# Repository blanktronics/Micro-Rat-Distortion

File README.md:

# Overview
Micro Rat Distortion majorly influnced by Olinthus Designs mini effects.

The idea is simple, I wanted to challenge myself by trying to recreate an extremely small version of the ProCo Rat distortion.

My secondary challenge is I want to create something even smaller than the Olinthus Desgin effects.

So far the dimesions of my project mostly mimcs the Olinthus dimensions except my assembly is 50mils wider and 50 mils thinner.

Next steps are to just shrink shrink shrink.

If you would like to try this out for yourself, the KiCad project I've designed can found in this repository!

## Pictures
Here are some pictures of the progress so far.

|  |  |  |  |
| ------- | ------- | ------- | ------- |
|  |  |  |  |
|  | |

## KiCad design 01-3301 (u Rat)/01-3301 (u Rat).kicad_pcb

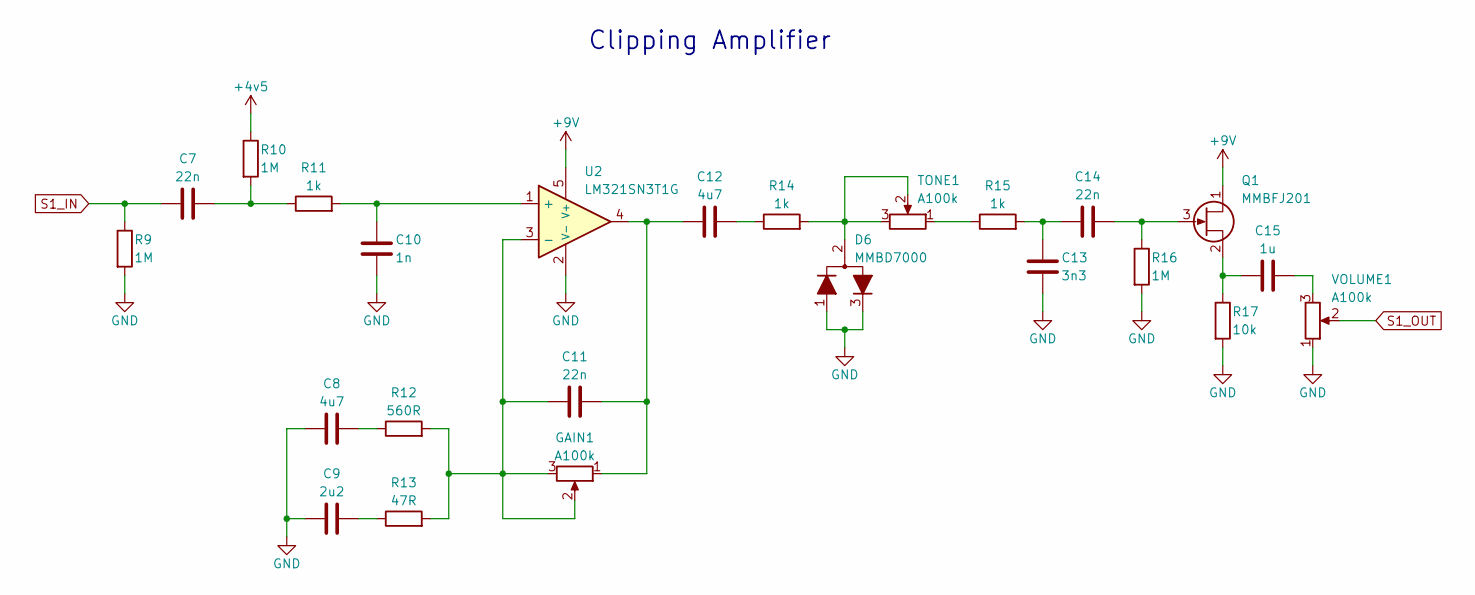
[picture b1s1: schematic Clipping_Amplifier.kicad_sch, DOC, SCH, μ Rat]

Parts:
C7, C11, C14: 22n; C_0402_1005Metric
C8, C12: 4u7; C_0603_1608Metric
C9: 2u2; C_0603_1608Metric
C10: 1n; C_0402_1005Metric
C13: 3n3; C_0402_1005Metric
C15: 1u; C_0603_1608Metric
D6: MMBD7000; SOT-23-3
GAIN1: A100k; Potentiometer_Alpha_RD901F-40-00D_Single_Vertical
Q1: MMBFJ201; SOT-23; Manufacturer_Part_Number MMBFJ201; Mouser Part Number 512-MMBFJ201
R9, R10, R16: 1M; R_0402_1005Metric
R11, R14, R15: 1k; R_0402_1005Metric
R12: 560R; R_0402_1005Metric
R13: 47R; R_0402_1005Metric
R17: 10k; R_0402_1005Metric
TONE1: A100k; Potentiometer_Alpha_RD901F-40-00D_Single_Vertical
U2: LM321SN3T1G; SOT95P275X110-5N; Manufacturer_Part_Number LM321SN3T1G; Mouser Part Number 863-LM321SN3T1G
VOLUME1: A100k; Potentiometer_Alpha_RD901F-40-00D_Single_Vertical

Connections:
+4v5: R10.1; also elsewhere on the board
+9V: Q1.1 (D), U2.5 (V+); also elsewhere on the board
GND: C8.1, C9.1, C10.2, C13.2, D6.1 (A), D6.3 (K), R9.2, R16.2, R17.2, U2.2 (V-), VOLUME1.1; also elsewhere on the board
unnamed: C7.2, R10.2, R11.1
unnamed: C8.2, R12.1
unnamed: C9.2, R13.1
unnamed: C11.2, C12.1, GAIN1.1, U2.4
unnamed: C12.2, R14.1
unnamed: C13.1, C14.1, R15.2
unnamed: C15.2, VOLUME1.3
unnamed: D6.2 (common), R14.2, TONE1.2, TONE1.3
unnamed: C14.2, Q1.3 (G), R16.1
unnamed: C15.1, Q1.2 (S), R17.1
unnamed: R15.1, TONE1.1
unnamed: C10.1, R11.2, U2.1 (+)
unnamed: C11.1, GAIN1.2, GAIN1.3, R12.2, R13.2, U2.3 (-)
S1_IN: C7.1, R9.1; also elsewhere on the board
S1_OUT: VOLUME1.2; also elsewhere on the board

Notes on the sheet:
Clipping Amplifier

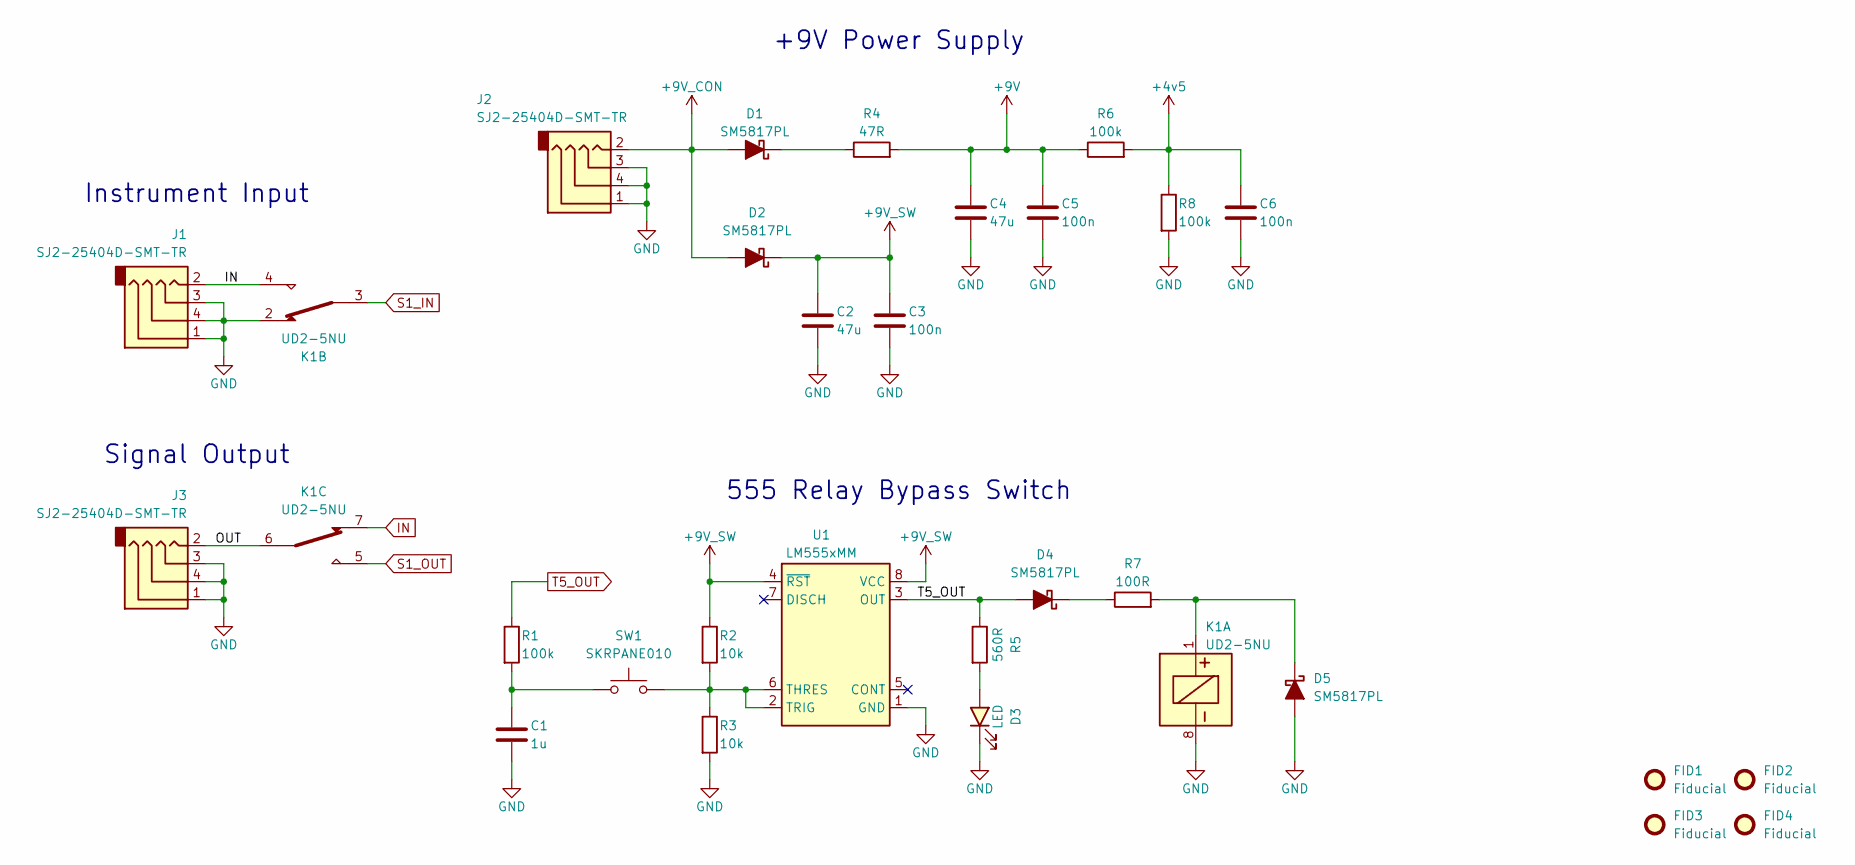
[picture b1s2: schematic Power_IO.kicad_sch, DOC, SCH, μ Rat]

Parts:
C1: 1u; C_0603_1608Metric
C2, C4: 47u; C_1210_3225Metric
C3, C5, C6: 100n; C_0402_1005Metric
D1, D2, D4, D5: SM5817PL; D_SOD-123
D3: LED; LED_0603_1608Metric
FID1, FID2, FID3, FID4: Fiducial; Fiducial_0.5mm_Mask1mm
J1, J2, J3: SJ2-25404D-SMT-TR; SJ225404DSMTTR; Manufacturer_Part_Number SJ2-25404D-SMT-TR; Mouser Part Number 490-SJ2-25404DSMT-TR
K1: UD2-5NU; UD25NUN; Manufacturer_Part_Number UD2-5NU; Mouser Part Number 551-UD2-5NU
R1, R6, R8: 100k; R_0402_1005Metric
R2, R3: 10k; R_0402_1005Metric
R4: 47R; R_0402_1005Metric
R5: 560R; R_0402_1005Metric
R7: 100R; R_0402_1005Metric
SW1: SKRPANE010
U1: LM555xMM; VSSOP-8_3x3mm_P0.65mm

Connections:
+4v5: C6.1, R6.2, R8.1; also elsewhere on the board
+9V: C4.1, C5.1, R4.2, R6.1; also elsewhere on the board
+9V_CON: D1.2 (A), D2.2 (A), J2.2 (TIP)
+9V_SW: C2.1, C3.1, D2.1 (K), R2.1, U1.4 (~RST), U1.8 (VCC)
/Power IO/OUT: J3.2 (TIP), K1.6 (COM_2)
GND: C1.2, C2.2, C3.2, C4.2, C5.2, C6.2, D3.1 (K), D5.2 (A), J1.1 (SLEEVE), J1.3 (RING1), J1.4 (RING2), J2.1 (SLEEVE), J2.3 (RING1), J2.4 (RING2), J3.1 (SLEEVE), J3.3 (RING1), J3.4 (RING2), K1.2 (NC_1), K1.8 (COIL_-), R3.2, R8.2, U1.1 (GND); also elsewhere on the board
IN: J1.2 (TIP), K1.4 (NO_1), K1.7 (NC_2)
unnamed: C1.1, R1.2, SW1.1
unnamed: D1.1 (K), R4.1
unnamed: D3.2 (A), R5.2
unnamed: D4.1 (K), R7.1
unnamed: D5.1 (K), K1.1 (COIL_+), R7.2
unnamed: R2.2, R3.1, SW1.2, U1.2 (TRIG), U1.6 (THRES)
S1_IN: K1.3 (COM_1); also elsewhere on the board
S1_OUT: K1.5 (NO_2); also elsewhere on the board
T5_OUT: D4.2 (A), R1.1, R5.1, U1.3 (OUT)

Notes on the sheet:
555 Relay Bypass Switch
Instrument Input
Signal Output
+9V Power Supply

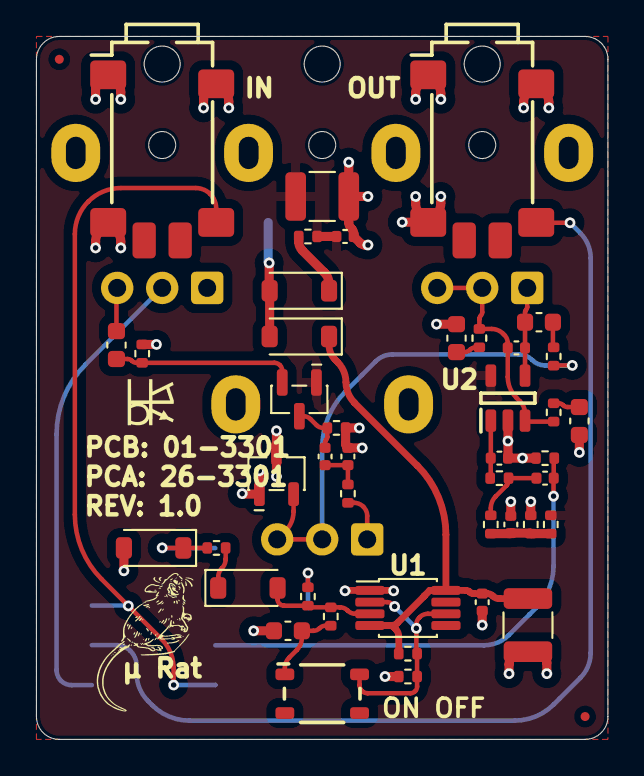
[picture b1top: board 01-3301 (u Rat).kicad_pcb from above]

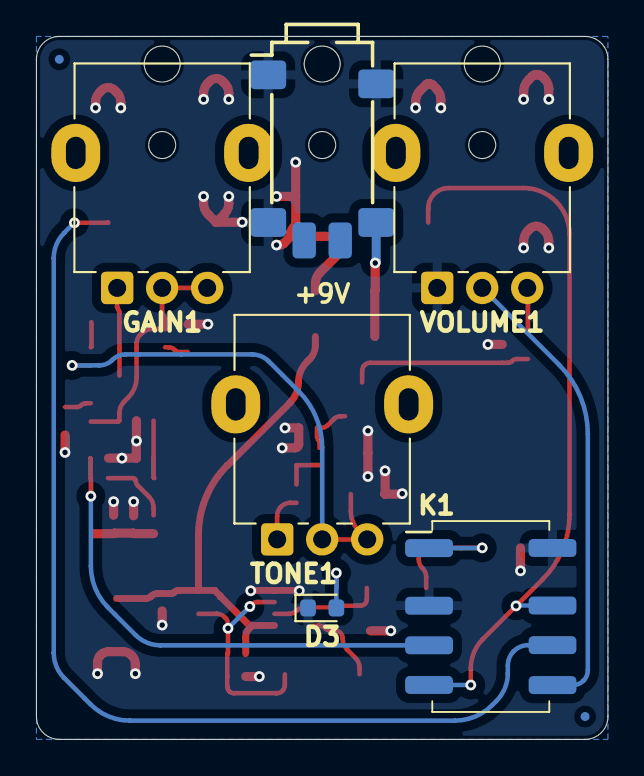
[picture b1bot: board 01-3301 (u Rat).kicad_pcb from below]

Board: 2 copper layers, 31.8 x 39.1 mm, 53 parts (8 on the bottom side), 29 nets.

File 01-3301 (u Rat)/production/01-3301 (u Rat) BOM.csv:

"Reference","Qty","Value","DNP","Exclude from BOM","Exclude from Board","Footprint","Description"
"C1,C15","2","1u","","","","Capacitor_SMD:C_0603_1608Metric","CAP CER 1uF +/-10% 50V X7R 0603"
"C2,C4","2","47u","","","","Capacitor_SMD:C_1210_3225Metric","CAP CER 47uF +/-10% 16V X7R 1210"
"C3,C5,C6","3","100n","","","","Capacitor_SMD:C_0402_1005Metric","CAP CER 100nF +/-10% 25V X7R 0402"
"C7,C11,C14","3","22n","","","","Capacitor_SMD:C_0402_1005Metric","CAP CER 22nF +/-10% 25V X7R 0402"
"C8,C12","2","4u7","","","","Capacitor_SMD:C_0603_1608Metric","CAP CER 4.7uF +/-10% 25V X7R 0603"
"C9","1","2u2","","","","Capacitor_SMD:C_0603_1608Metric","CAP CER 2.2uF +/-10% 25V X7R 0603"
"C10","1","1n","","","","Capacitor_SMD:C_0402_1005Metric","CAP CER 1nF +/-10% 25V X7R 0402"
"C13","1","3n3","","","","Capacitor_SMD:C_0402_1005Metric","CAP CER 3.3nF +/-10% 25V X7R 0402"
"D1,D2,D4,D5","4","SM5817PL","","","","Diode_SMD:D_SOD-123","20V 1A Schottky Diode SOD-123,~"
"D3","1","LED","","","","LED_SMD:LED_0603_1608Metric","Light emitting diode"
"D6","1","MMBD7000","","","","Package_TO_SOT_SMD:SOT-23-3","Dual diode, anode/center/cathode"
"GAIN1,TONE1,VOLUME1","3","A100k","","","","Potentiometer_Custom:Potentiometer_Alpha_RD901F-40-00D_Single_Vertical","Potentiometer 9mm A100k Log"
"J1,J2,J3","3","SJ2-25404D-SMT-TR","","","","SamacSys_Parts:SJ225404DSMTTR","SJ2-25404D-SMT-TR - 2.5 mm, Stereo, Right Angle, Surface Mount (SMT), 4 Conductors, 2 Internal Switches, Audio Jack Connector"
"K1","1","UD2-5NU","","","","UD25NUN","KEMET, UD2, Relays, Signal, 5 V, 220 V, 250 VAC, 1 A, 100 mOhms, 1 GOhms, 10.6mm, 6.5mm, 5.45mm"
"Q1","1","MMBFJ201","","","","Package_TO_SOT_SMD:SOT-23","N-Channel General Purpose Amplifier"
"R1,R6,R8","3","100k","","","","Resistor_SMD:R_0402_1005Metric","RES SMD 100k OHM 1% 1/16W 0402"
"R2,R3,R17","3","10k","","","","Resistor_SMD:R_0402_1005Metric","RES SMD 10k OHM 1% 1/16W 0402"
"R4,R13","2","47R","","","","Resistor_SMD:R_0402_1005Metric","RES SMD 47 OHM 1% 1/16W 0402"
"R5,R12","2","560R","","","","Resistor_SMD:R_0402_1005Metric","RES SMD 560 OHM 1% 1/16W 0402"
"R7","1","100R","","","","Resistor_SMD:R_0402_1005Metric","RES SMD 100 OHM 1% 1/16W 0402"
"R9,R10,R16","3","1M","","","","Resistor_SMD:R_0402_1005Metric","RES SMD 1M OHM 1% 1/16W 0402"
"R11,R14,R15","3","1k","","","","Resistor_SMD:R_0402_1005Metric","RES SMD 1k OHM 1% 1/16W 0402"
"SW1","1","SKRPANE010","","","","SamacSys_Parts:SKRPANE010","Tactile Switches 500mOhm 1.57N 16VDC 4.2X3.2X2.5MM 50mA"
"U1","1","LM555xMM","","","","Package_SO:VSSOP-8_3x3mm_P0.65mm","Precision Timer, 555 compatible, VSSOP-8"
"U2","1","LM321SN3T1G","","","","SamacSys_Parts:SOT95P275X110-5N","Unity Gain Stable with 1.5 nF Capacitive Load; Wide Supply Voltage Range: 3 V to 32 V; Short Circuit Protected Outputs; True Differential Input Stage; Low Input Bias Currents; Internally Compensated; Single and Split Supply Operation"
